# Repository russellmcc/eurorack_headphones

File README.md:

This is a tested design for a small headphone amp/line output module for eurorack modular synthesizers.

Most of the construction is SMT, with the exception of user-replaceable socketted op-amps.

Please use the BOM.txt to order parts.

This is 5hp and uses 20mA current.

This work is licensed under a [Creative Commons Attribution-ShareAlike 3.0 Unported License.](http://creativecommons.org/licenses/by-sa/3.0/deed.en_US)

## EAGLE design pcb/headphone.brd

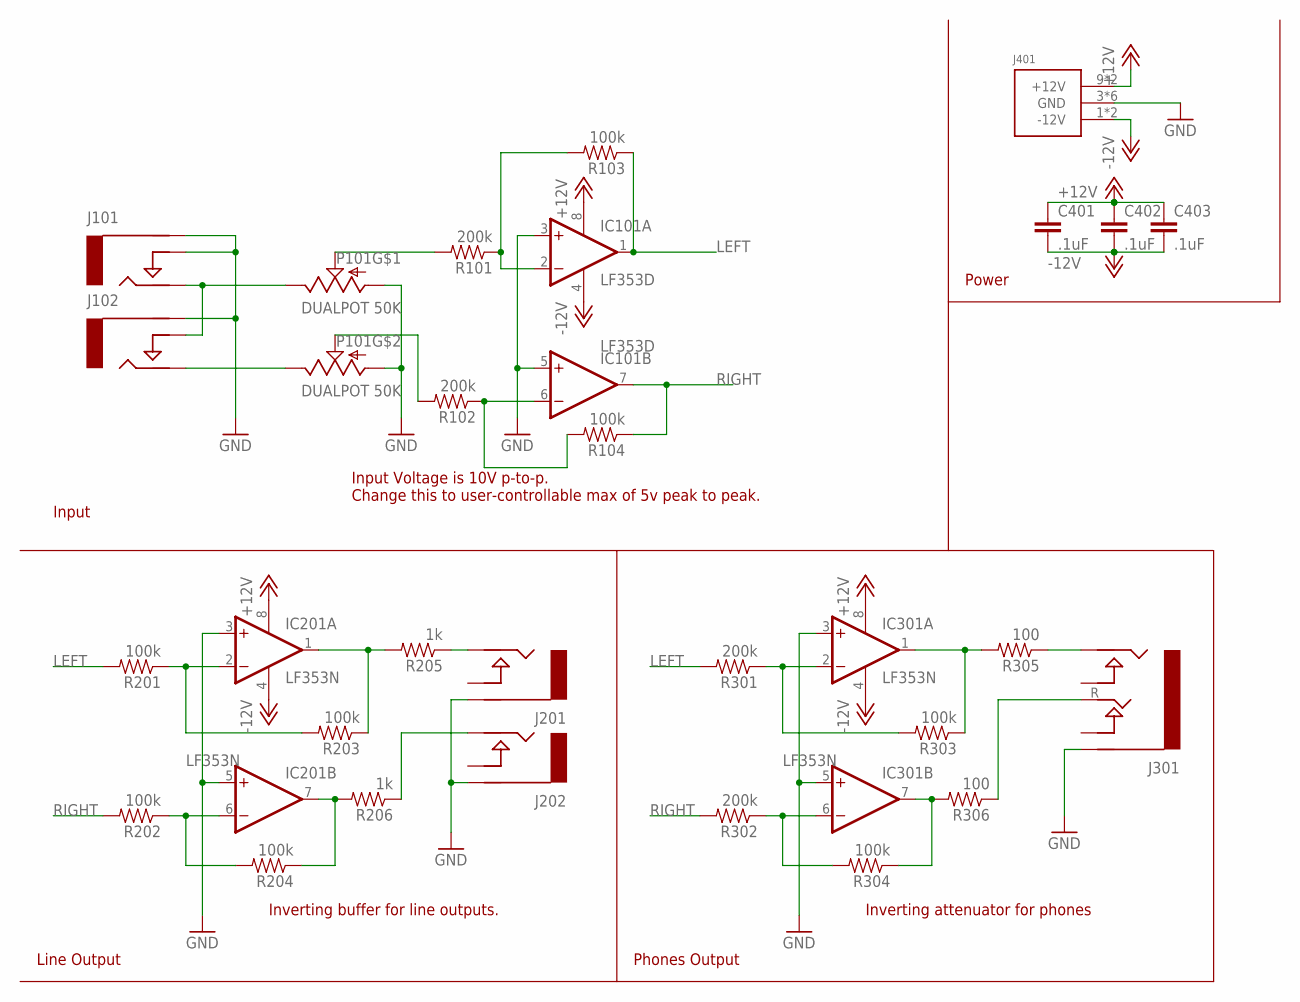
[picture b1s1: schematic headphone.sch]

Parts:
C401, C402, C403: .1uF; 0603-CAP
IC101: LF353D; SO08
IC201, IC301: LF353N; DIL08
J101, J102: MONOJACKSWITCHCRAFT3; SWITCHCRAFT_35RAPC2AV
J201, J202: MONOJACKNEUTRIK; NEUTRIK_NMJ4HHD2
J301: STEREOJACK; NEUTRIK_NMJ6HFD2
J401: POWER_SIMPLE16; POWER_16
P101: DUALPOT 50K; ALPSRK09L12B0A31
R101, R102, R301, R302: 200k; 0603-RES
R103, R104, R201, R202, R203, R204, R303, R304: 100k; 0603-RES
R205, R206: 1k; 0603-RES
R305, R306: 100; 0603-RES

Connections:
+12V: C401.1, C402.1, C403.1, IC101.8 (V+), IC201.8 (V+), IC301.8 (V+), J401.9 (+12V), J401.10 (+12V)
-12V: C401.2, C402.2, C403.2, IC101.4 (V-), IC201.4 (V-), IC301.4 (V-), J401.1 (-12V), J401.2 (-12V)
GND: IC101.3 (+IN), IC101.5 (+IN), IC201.3 (+IN), IC201.5 (+IN), IC301.3 (+IN), IC301.5 (+IN), J101.S (SLEEVE), J101.TN (NORM), J102.S (SLEEVE), J201.S (SLEEVE), J201.SN (SLEEVE), J202.S (SLEEVE), J202.SN (SLEEVE), J301.S (SLEEVE), J301.SN (SLEEVE), J401.3 (GND), J401.4 (GND), J401.5 (GND), J401.6 (GND), J401.7 (GND), J401.8 (GND), P101.D1 (A), P101.D2 (A)
J102: J101.T (TIP), J102.TN (NORM), P101.U1 (E)
LEFT: IC101.1 (OUT), R103.1, R201.2, R301.2
unnamed: IC101.6 (-IN), R102.1, R104.2
unnamed: P101.W2 (S), R102.2
unnamed: P101.W1 (S), R101.2
unnamed: IC101.2 (-IN), R101.1, R103.2
unnamed: J102.T (TIP), P101.U2 (E)
unnamed: IC201.7 (OUT), R204.1, R206.2
unnamed: IC201.6 (-IN), R202.1, R204.2
unnamed: IC201.2 (-IN), R201.1, R203.2
unnamed: IC201.1 (OUT), R203.1, R205.2
unnamed: IC301.7 (OUT), R304.1, R306.2
unnamed: J201.T (TIP), R205.1
unnamed: J202.T (TIP), R206.1
unnamed: IC301.6 (-IN), R302.1, R304.2
unnamed: IC301.2 (-IN), R301.1, R303.2
unnamed: IC301.1 (OUT), R303.1, R305.2
unnamed: J301.T (TIP), R305.1
unnamed: J301.R (RING), R306.1
RIGHT: IC101.7 (OUT), R104.1, R202.2, R302.2

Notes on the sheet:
Input Voltage is 10V p-to-p. Change this to user-controllable max of 5v peak to peak.
Input
Inverting buffer for line outputs.
Line Output
Inverting attenuator for phones
Phones Output
Power

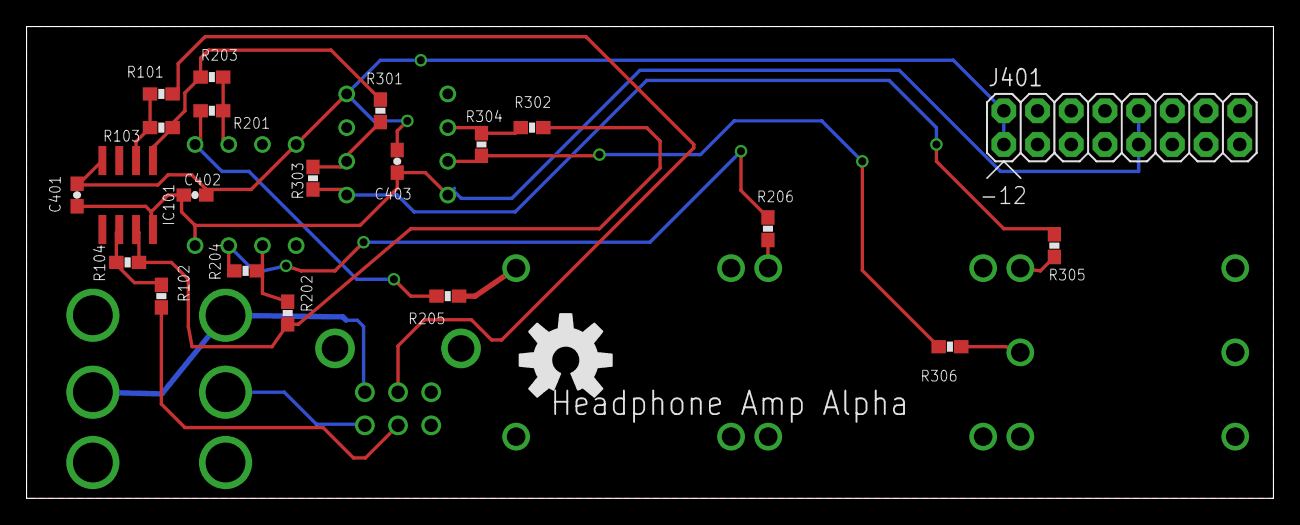
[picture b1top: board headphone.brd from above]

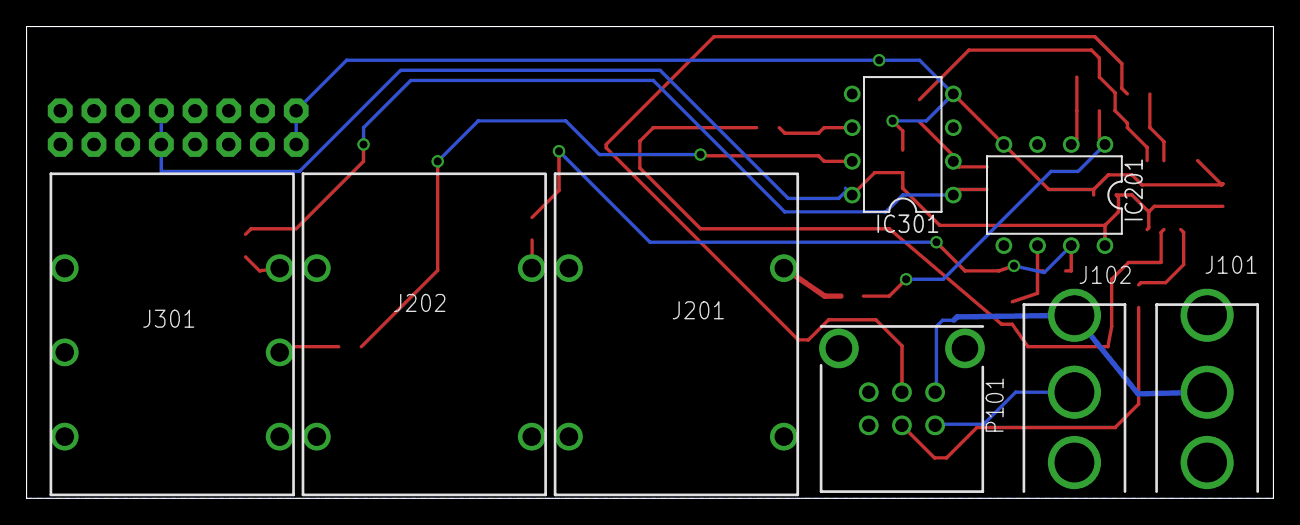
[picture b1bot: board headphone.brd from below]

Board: 2 copper layers, 94.0 x 35.6 mm, 30 parts (8 on the bottom side), 23 nets.

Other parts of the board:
U$1: OSHW-LOGO-L

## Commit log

2013-02-06 initial version of headphone amp
2013-02-07 Added gitignore and a BOM
2013-02-07 Added README with CC license
2013-02-07 finished parting out the BOM from mouser
2013-02-14 added silkscreen
2013-02-14 layers
2013-02-14 Panel!
2013-03-14 solder mask!
2013-04-08 fix for backwards volume knob and too-small text
2013-04-08 fixed front panel
2013-05-15 update readme with specs
2017-06-08 WIP new kicad design
2017-06-08 Update panel
2017-06-08 Update pcb
2017-06-08 Fix for BOM
2017-06-29 Fix errors on board

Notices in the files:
parts and their libraries:
SparkFun: Licensing: CC v3.0 Share-Alike You are welcome to use this library for commercial purposes.
